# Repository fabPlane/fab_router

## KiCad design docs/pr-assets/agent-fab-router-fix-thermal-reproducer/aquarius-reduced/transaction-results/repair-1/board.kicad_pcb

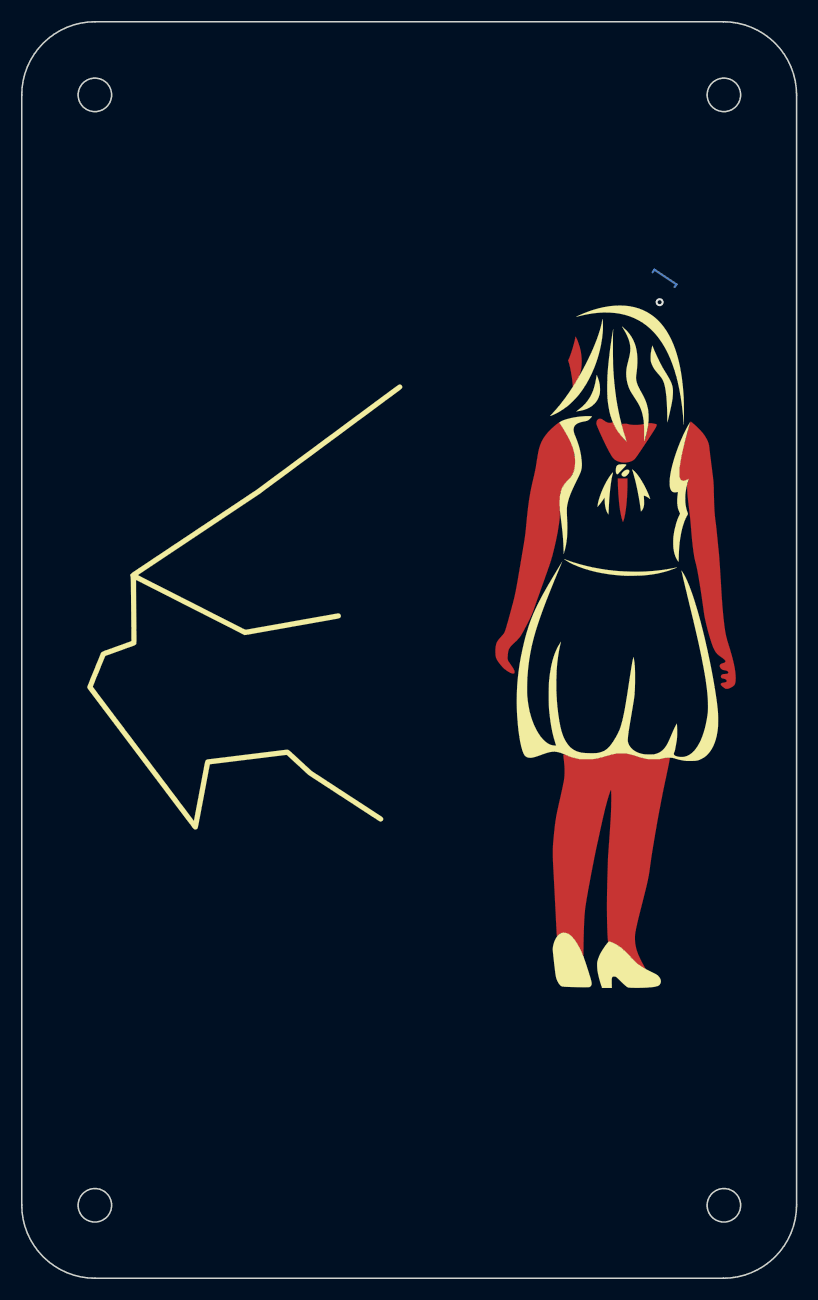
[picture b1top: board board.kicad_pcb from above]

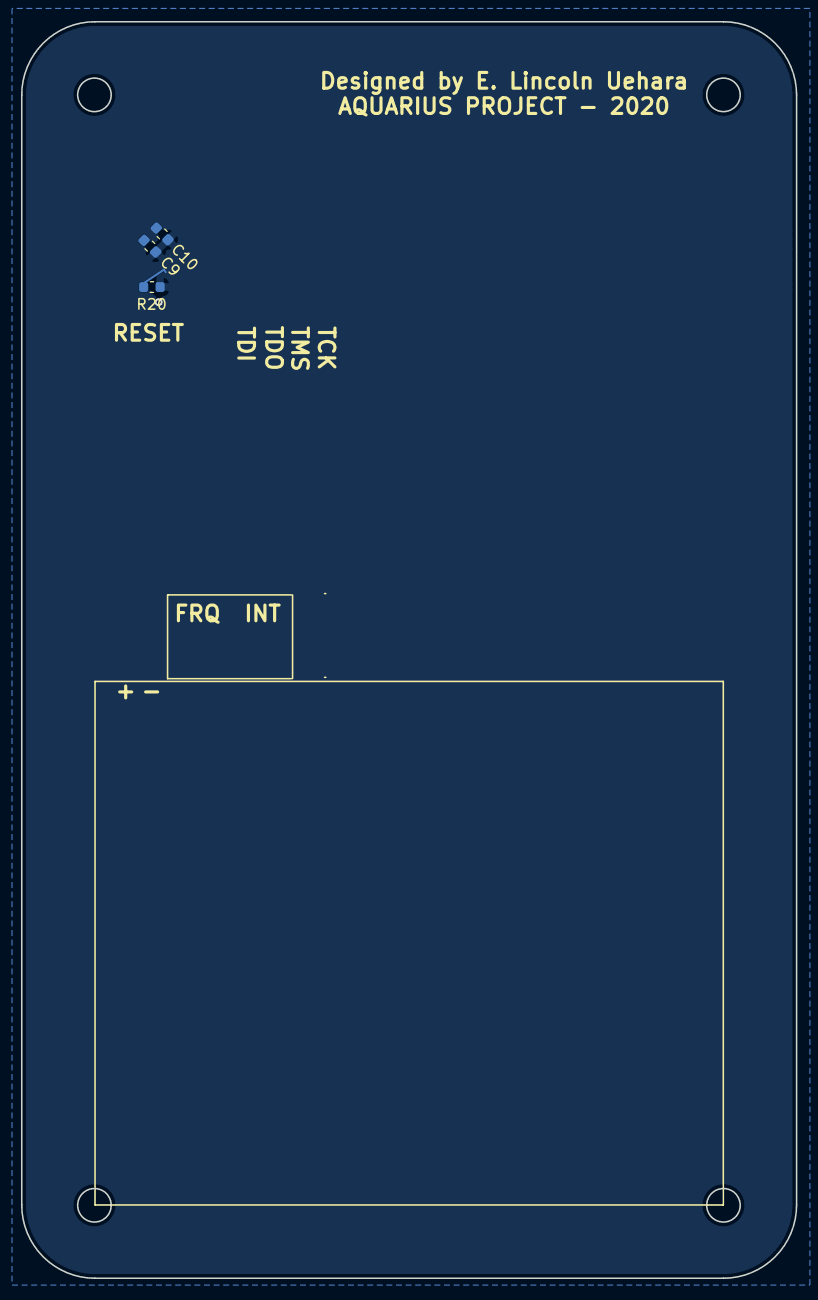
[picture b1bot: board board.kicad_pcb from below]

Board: 2 copper layers, 74.0 x 120.0 mm, 4 parts (3 on the bottom side), 2 nets.

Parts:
C9: 0.01uF; C_0603_1608Metric
C10: 0.1uF; C_0603_1608Metric
R20: 0; R_0603_1608Metric
X1: theGirl

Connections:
+3V3: C9.1, C10.1
GNDD: C9.2, C10.2, R20.1

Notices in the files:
docs/pr-assets/agent-fab-router-fix-thermal-reproducer/aquarius-reduced/transaction-results/repair-1/board.kicad_pcb:
creativecommons.org/licenses/by/4.0
License: CC BY 4.0
